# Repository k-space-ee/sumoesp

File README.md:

# SumoESP

SumoESP is a [ESP32](https://espressif.com/en/products/hardware/esp32/overview)
based sumorobot similar to [SumoCHIP](https://github.com/eik-robo/sumochip).

Why yet another sumorobot design?

* SumoCHIP has it's issues listed under [known issues](https://github.com/eik-robo/sumochip#known-issues) section
* ESP32 has wireless interface and supports WebSockets which means we can keep same level of functionality
* ESP32 has hardware ADC-s which can be used with traditional IR distance
  sensors such as Sharp [Sharp GP2Y0A21YK0F](https://www.pololu.com/product/136)
* ESP32 has hardware PWM-s which means no more jerky behaviour with cheap servos
* ESP32 has just enough juice to run Micropython, so we don't have to rewrite everything

## Getting Micropython running

Fetch Xtensa toolchain, Espressif IoT Development Framework and Micropython fork:

```bash
wget https://dl.espressif.com/dl/xtensa-esp32-elf-linux64-1.22.0-61-gab8375a-5.2.0.tar.gz
tar xvf xtensa-esp32-elf-linux64-1.22.0-61-gab8375a-5.2.0.tar.gz

git clone https://github.com/espressif/esp-idf
cd esp-idf
git submodule update --init
git checkout f73c6f875cc564fa6c9962be71eac4dbdc56aa63
cd ..

git clone https://github.com/vandys/micropython-esp32/
cd micropython-esp32
git checkout e94cde8a735926ace3f6efe79cbc2b9ee83a9ee3
git submodule update --init
make -C mpy-cross
cd esp32
ESPIDF=../../esp-idf/ PATH=../../xtensa-esp32-elf/bin/:$PATH make deploy
```

Open up serial via USB cable:

```python
import machine
motor_left = machine.PWM(machine.Pin(34), 50)
motor_right = machine.PWM(machine.Pin(13), 50)
motor_left.duty(40)
motor_left.duty(77)
motor_left.duty(135)
```

## Bill of materials

Preliminary bill of materials:

- ESP32 4USD
- LiPo cell 3 USD
- Wheels 3 USD each
- Servos 6 USD each
- Ultrasonic distance sensor 1.3 USD or Sharp infrared sensors
- LiPo charger and protection module 1.5 USD
- LITEON LTH-209-01 sensors for line following 0.30 EUR each

Total less than 30USD, excluding either 3D printed case or DIY metal frame.

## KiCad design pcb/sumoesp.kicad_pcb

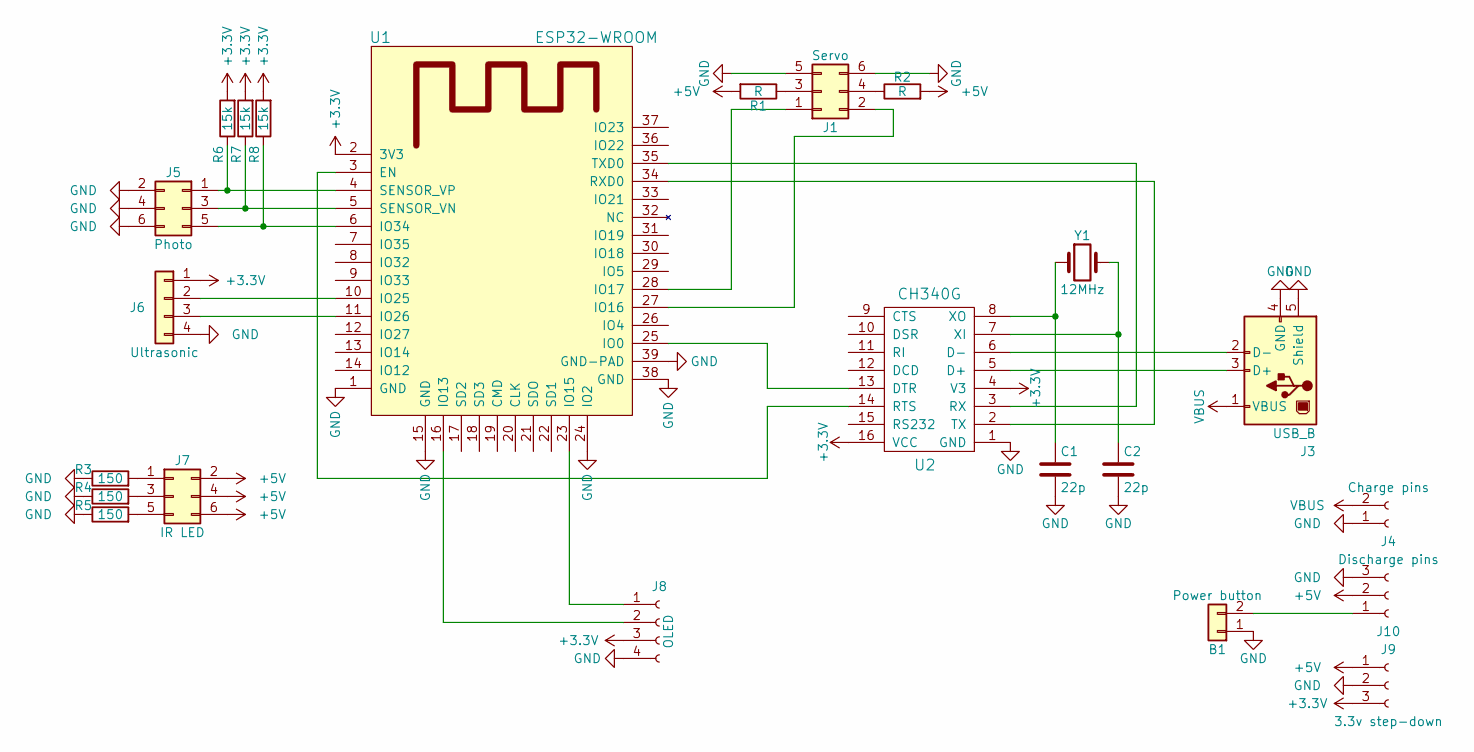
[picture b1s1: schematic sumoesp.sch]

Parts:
B1: Power button; SW_Tactile_SPST_Angled_PTS645Vx83-2LFS
C1, C2: 22p; C_Disc_D4.3mm_W1.9mm_P5.00mm
J1: Servo; Pin_Header_Angled_2x03_Pitch2.54mm
J3: USB_B
J4: Charge pins; Socket_Strip_Angled_1x02_Pitch2.54mm
J5: Photo; Pin_Header_Angled_2x03_Pitch2.54mm
J6: Ultrasonic; Pin_Header_Angled_1x04_Pitch2.54mm
J7: IR LED; Pin_Header_Angled_2x03_Pitch2.54mm
J8: OLED; Socket_Strip_Straight_1x04_Pitch2.54mm
J9: 3.3v step-down; Socket_Strip_Angled_1x03_Pitch2.54mm
J10: Discharge pins; Socket_Strip_Angled_1x03_Pitch2.54mm
R1, R2: R; R_Axial_DIN0207_L6.3mm_D2.5mm_P10.16mm_Horizontal
R3, R4, R5: 150; R_Axial_DIN0207_L6.3mm_D2.5mm_P7.62mm_Horizontal
R6, R7, R8: 15k; R_Axial_DIN0207_L6.3mm_D2.5mm_P7.62mm_Horizontal
U1: ESP32-WROOM
U2: CH340G; SOP-16_4.4x10.4mm_Pitch1.27mm
Y1: 12MHz; Crystal_HC49-U_Vertical

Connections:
+3V3: J6.1, J8.3, J9.3, R6.2, R7.2, R8.2, U1.2 (3V3), U2.4 (V3), U2.16 (VCC)
+5V: J7.2, J7.4, J7.6, J9.1, J10.2, R1.2, R2.2
GND: B1.1, C1.2, C2.2, J1.5, J1.6, J3.4 (GND), J3.5 (Shield), J4.1, J5.2, J5.4, J5.6, J6.4, J8.4, J9.2, J10.3, R3.1, R4.1, R5.1, U1.1 (GND), U1.15 (GND), U1.24 (IO2), U1.38 (GND), U1.39 (GND-PAD), U2.1 (GND)
unnamed: B1.2, J10.1
unnamed: C1.1, U2.8 (XO), Y1.1
unnamed: C2.1, U2.7 (XI), Y1.2
unnamed: J1.1, U1.28 (IO17)
unnamed: J1.2, U1.27 (IO16)
unnamed: J1.3, R1.1
unnamed: J1.4, R2.1
unnamed: J3.2 (D-), U2.6 (D-)
unnamed: J3.3 (D+), U2.5 (D+)
unnamed: J5.1, R6.1, U1.4 (SENSOR_VP)
unnamed: J5.3, R7.1, U1.5 (SENSOR_VN)
unnamed: J5.5, R8.1, U1.6 (IO34)
unnamed: J6.2, U1.10 (IO25)
unnamed: J6.3, U1.11 (IO26)
unnamed: J7.1, R3.2
unnamed: J7.3, R4.2
unnamed: J7.5, R5.2
unnamed: J8.1, U1.23 (IO15)
unnamed: J8.2, U1.16 (IO13)
unnamed: U1.3 (EN), U2.14 (RTS)
unnamed: U1.25 (IO0), U2.13 (DTR)
unnamed: U1.34 (RXD0), U2.2 (TX)
unnamed: U1.35 (TXD0), U2.3 (RX)
VBUS: J3.1 (VBUS), J4.2

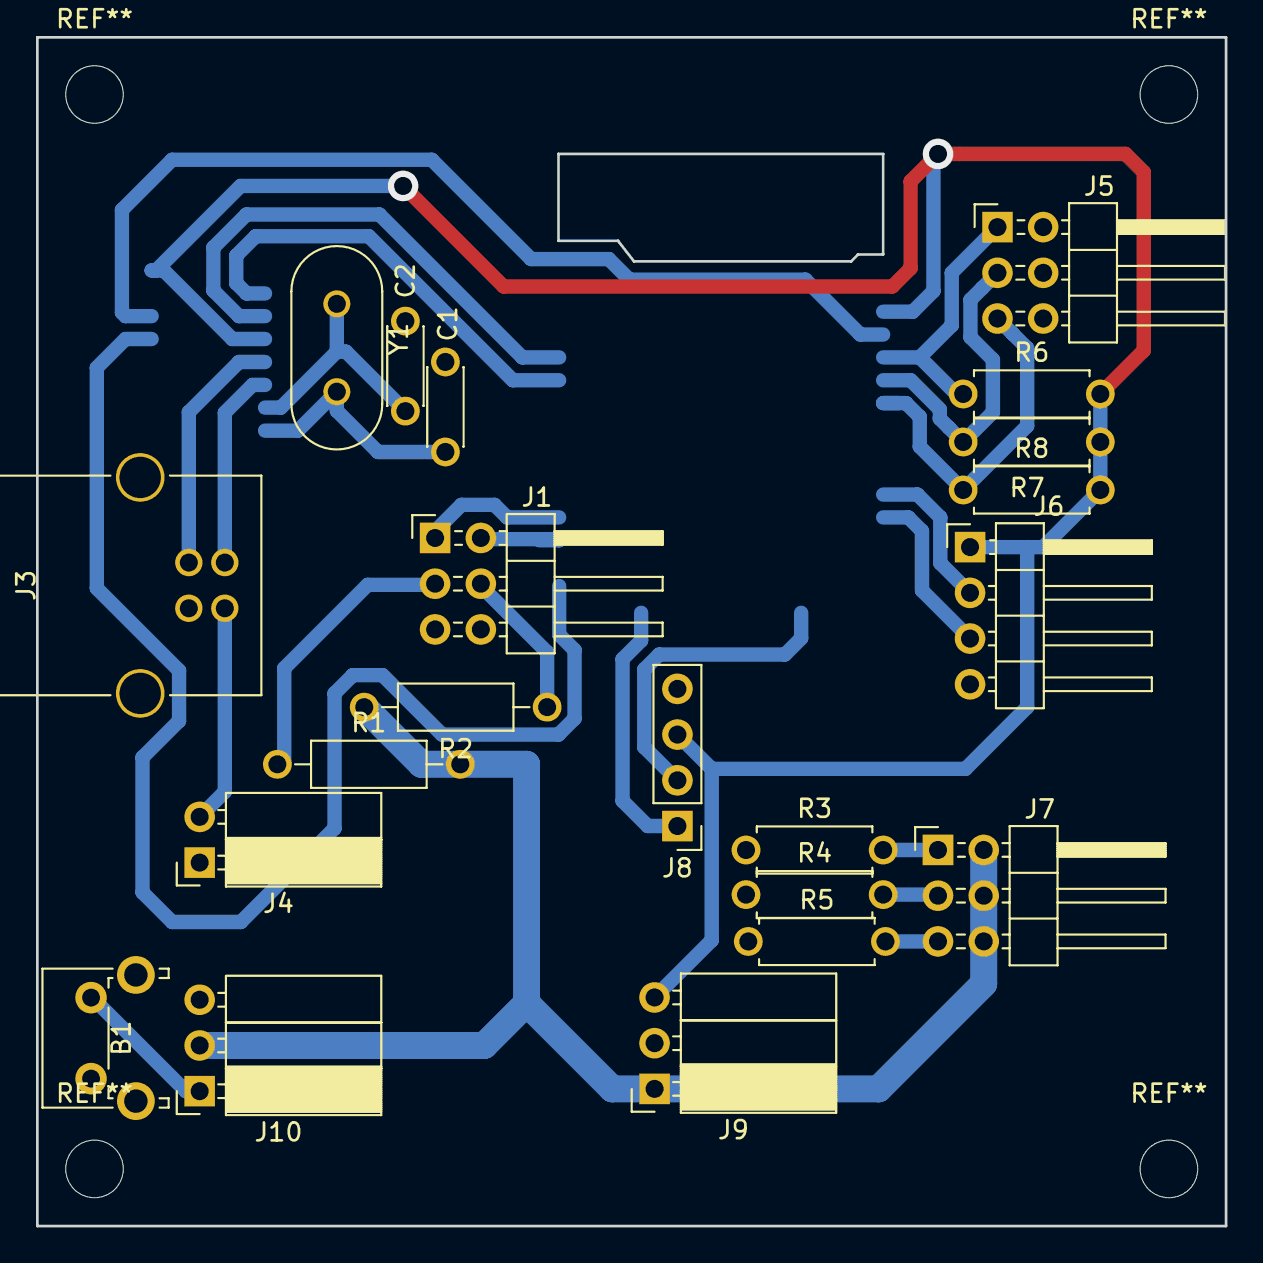
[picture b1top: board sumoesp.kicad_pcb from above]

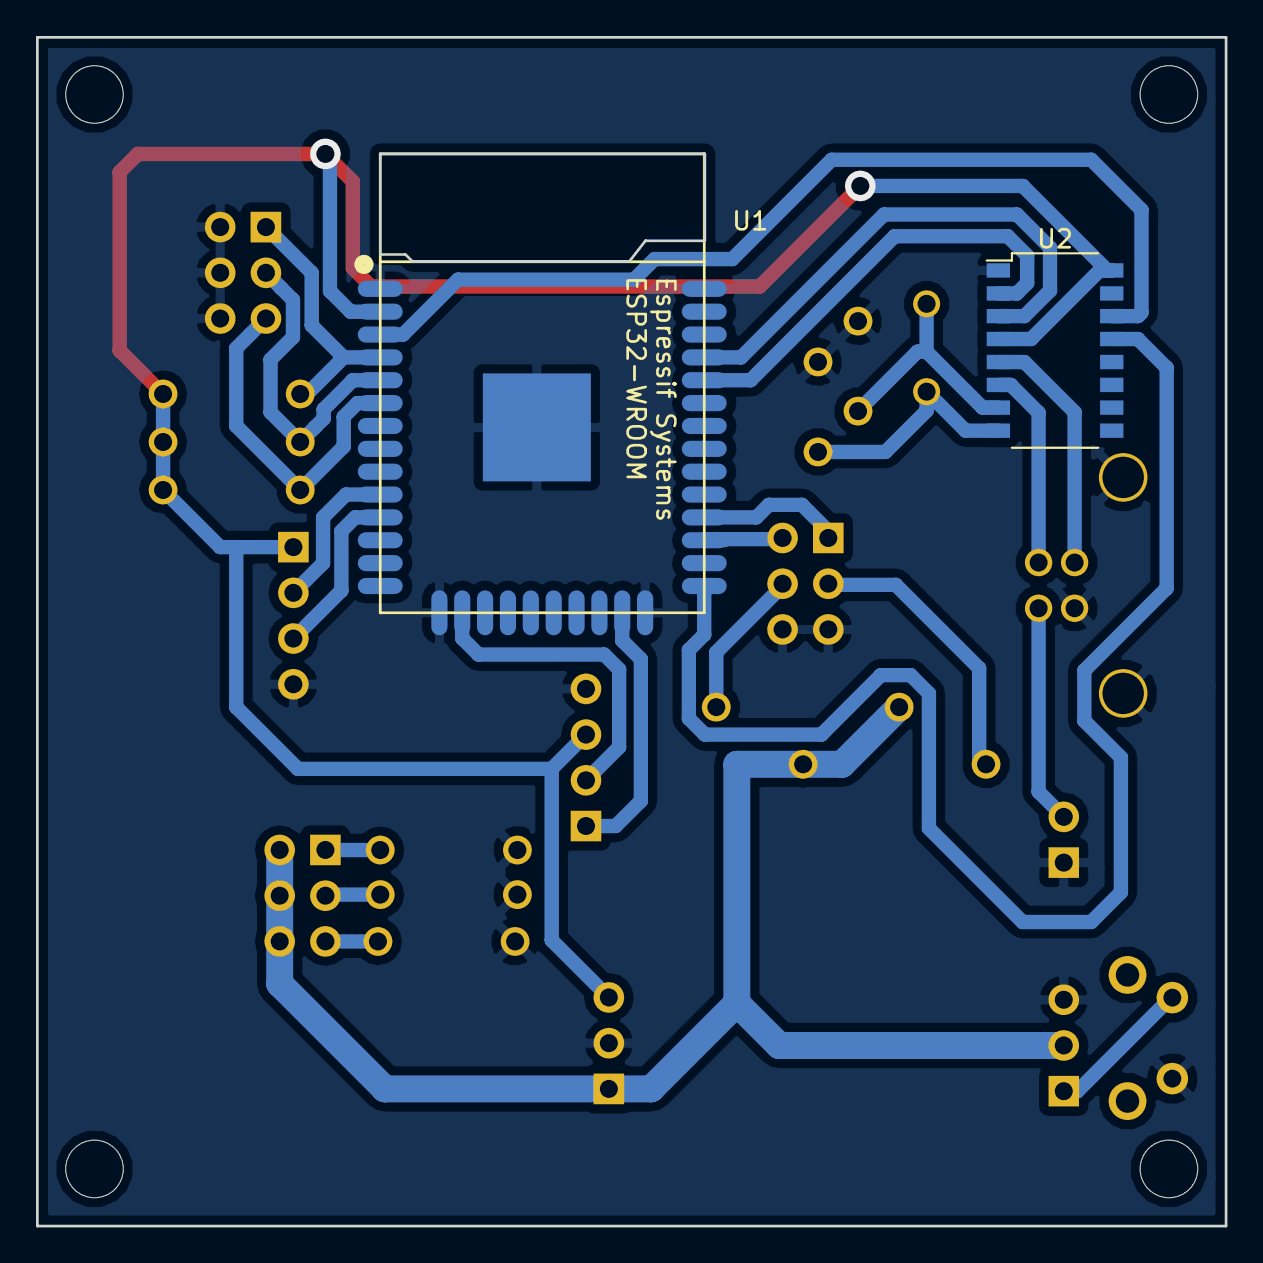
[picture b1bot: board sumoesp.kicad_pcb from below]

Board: 2 copper layers, 66.0 x 66.0 mm, 23 parts (2 on the bottom side), 27 nets.

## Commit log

2018-04-16 add contributors file
2018-04-16 update gitignore
2018-04-16 add sumorobot firmware
2018-04-16 add KiCad files
2018-05-06 update pcb layout
